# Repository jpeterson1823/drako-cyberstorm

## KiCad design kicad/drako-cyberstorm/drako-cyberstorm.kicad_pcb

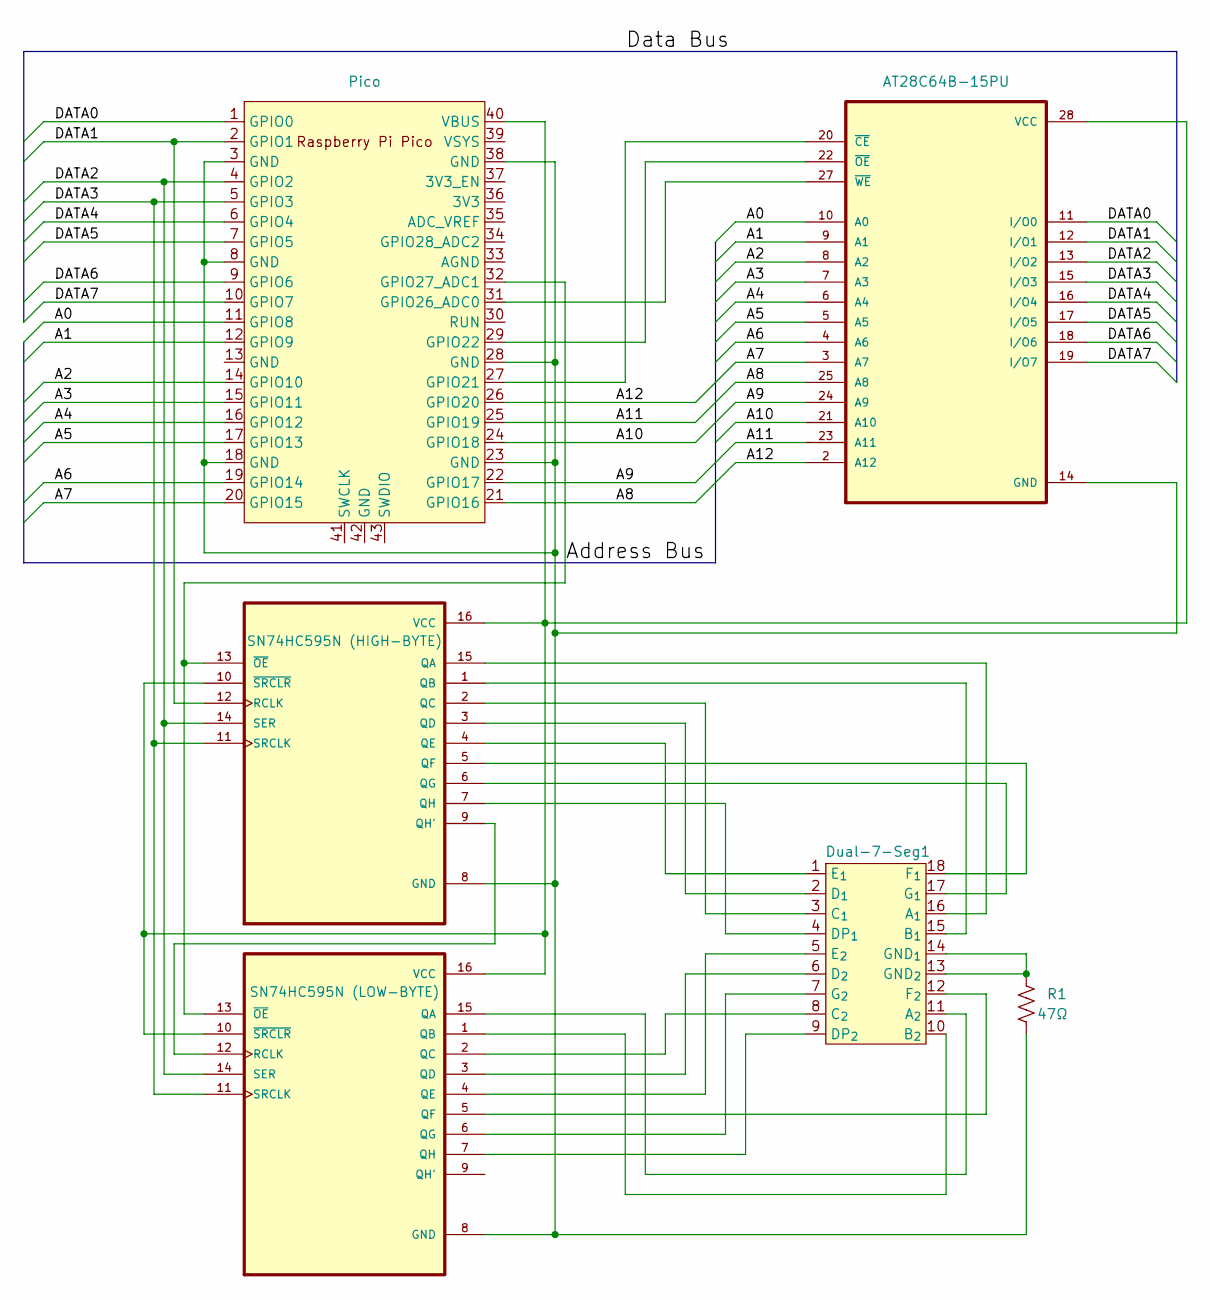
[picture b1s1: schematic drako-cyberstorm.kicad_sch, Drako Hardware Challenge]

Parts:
Dual-7-Seg1: LDD-C514RI
R1: 47Ω; R_Axial_DIN0207_L6.3mm_D2.5mm_P10.16mm_Horizontal
U1: Pico; RPi_Pico_SMD_TH
U2: AT28C64B-15PU; DIP1555W45P254L3733H482Q28; PARTREV B
U3: SN74HC595N (HIGH-BYTE); DIP794W45P254L1969H508Q16; DigiKey_Part_Number 296-1600-5-ND
U4: SN74HC595N (LOW-BYTE); DIP794W45P254L1969H508Q16; DigiKey_Part_Number 296-1600-5-ND

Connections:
/A0: U1.11 (GPIO8), U2.10 (A0)
/A1: U1.12 (GPIO9), U2.9 (A1)
/A2: U1.14 (GPIO10), U2.8 (A2)
/A3: U1.15 (GPIO11), U2.7 (A3)
/A4: U1.16 (GPIO12), U2.6 (A4)
/A5: U1.17 (GPIO13), U2.5 (A5)
/A6: U1.19 (GPIO14), U2.4 (A6)
/A7: U1.20 (GPIO15), U2.3 (A7)
/A8: U1.21 (GPIO16), U2.25 (A8)
/A9: U1.22 (GPIO17), U2.24 (A9)
/A10: U1.24 (GPIO18), U2.21 (A10)
/A11: U1.25 (GPIO19), U2.23 (A11)
/A12: U1.26 (GPIO20), U2.2 (A12)
/DATA0: U1.1 (GPIO0), U2.11 (I/O0)
/DATA1: U1.2 (GPIO1), U2.12 (I/O1), U3.12 (RCLK)
/DATA2: U1.4 (GPIO2), U2.13 (I/O2), U3.14 (SER), U4.14 (SER)
/DATA3: U1.5 (GPIO3), U2.15 (I/O3), U3.11 (SRCLK), U4.11 (SRCLK)
/DATA4: U1.6 (GPIO4), U2.16 (I/O4)
/DATA5: U1.7 (GPIO5), U2.17 (I/O5)
/DATA6: U1.9 (GPIO6), U2.18 (I/O6)
/DATA7: U1.10 (GPIO7), U2.19 (I/O7)
unnamed: Dual-7-Seg1.16 (A_{1}), U3.15 (QA)
unnamed: Dual-7-Seg1.11 (A_{2}), U4.15 (QA)
unnamed: Dual-7-Seg1.15 (B_{1}), U3.1 (QB)
unnamed: Dual-7-Seg1.10 (B_{2}), U4.1 (QB)
unnamed: Dual-7-Seg1.3 (C_{1}), U3.2 (QC)
unnamed: Dual-7-Seg1.8 (C_{2}), U4.2 (QC)
unnamed: Dual-7-Seg1.4 (DP_{1}), U3.7 (QH)
unnamed: Dual-7-Seg1.9 (DP_{2}), U4.7 (QH)
unnamed: Dual-7-Seg1.2 (D_{1}), U3.3 (QD)
unnamed: Dual-7-Seg1.6 (D_{2}), U4.3 (QD)
unnamed: Dual-7-Seg1.1 (E_{1}), U3.4 (QE)
unnamed: Dual-7-Seg1.5 (E_{2}), U4.4 (QE)
unnamed: Dual-7-Seg1.18 (F_{1}), U3.5 (QF)
unnamed: Dual-7-Seg1.12 (F_{2}), U4.5 (QF)
unnamed: Dual-7-Seg1.13 (GND_{2}), Dual-7-Seg1.14 (GND_{1}), R1.1
unnamed: Dual-7-Seg1.17 (G_{1}), U3.6 (QG)
unnamed: Dual-7-Seg1.7 (G_{2}), U4.6 (QG)
unnamed: U1.27 (GPIO21), U2.20 (~CE)
unnamed: U1.29 (GPIO22), U2.22 (~OE)
unnamed: U1.31 (GPIO26_ADC0), U2.27 (~WE)
unnamed: U1.32 (GPIO27_ADC1), U3.13 (~OE), U4.13 (~OE)
unnamed: U1.40 (VBUS), U2.28 (VCC), U3.10 (~SRCLR), U3.16 (VCC), U4.10 (~SRCLR), U4.16 (VCC)
unnamed: R1.2, U1.3 (GND), U1.8 (GND), U1.18 (GND), U1.23 (GND), U1.28 (GND), U1.38 (GND), U2.14 (GND), U3.8 (GND), U4.8 (GND)
unnamed: U3.9 (QH'), U4.12 (RCLK)

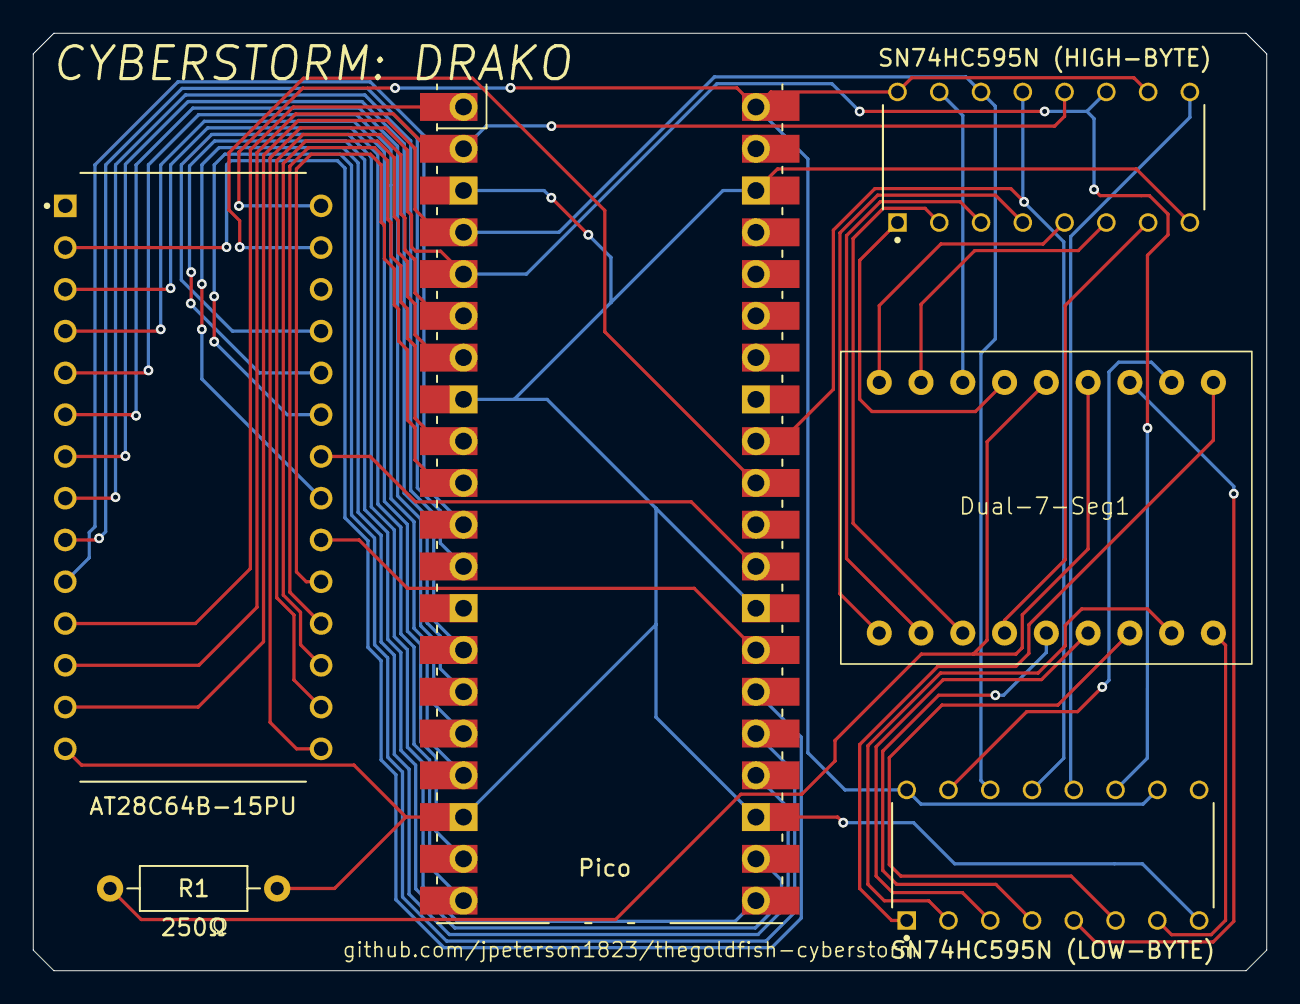
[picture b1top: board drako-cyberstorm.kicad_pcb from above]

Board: 2 copper layers, 75.0 x 57.0 mm, 6 parts (0 on the bottom side), 45 nets.

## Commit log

2024-12-25 Initializing this repo.
    Created:
    * SN74HC595 basic HAL
    * LDD-C514RI basic API (display)
    * Very basic hexidecimal Serial CLI
2025-01-01 HAL/API basic implementation completed.
    Basic control API for the display and HAL/API for the EEPROM is
    complete.
    Datasheet for EEPROM has been added.
2025-01-03 Completed PCB
    PCB for this challenge has been completed.
2025-01-03 Added the drawing sheet for KiCAD schematic and footprint
    Drawing sheet for this design was not included in the previous push. Adding it now.
2025-01-04 Started work on Drako's terminal and updated CMakeLists.
    CMakeLists was updated to use `pico-sdk` as a git submodule to aid in
    modularity of this repo.
2025-01-04 Renamed board to DRAKO & refactored code to match.
2025-01-04 Modified CMakeLists to use `pico-sdk` as submodule.
2025-01-22 Added early doxygen & continuing terminal progress.
2025-01-22 Implemented Randomized Full-Integration Test
2025-01-23 Fixed includes and made randomized test output more robust.
2025-01-23 Cleaned code up a bit and optimized terminal-api a little.
    TODO: terminal_get_command(...) still needs to split string and store
    arguments into the tcmd_t buffer.
2025-01-23 Terminal API completed. Started work on Drako's default commands.
2025-01-24 Refactored terminal-api code due to absolutely massively messing it up the first time.
2025-01-25 Terminal API optimizations and two new default commands.
    Removed all heap allocations and replaced them with stack allocations to
    avoid heap fragmentation. String manipulation was also made faster and
    safer by utilizing strtok_r and having robust null terminator
    guarantees.
    Two new commands: show and hide.
    Show displays a byte on the display.
2025-01-25 Removed merge artifact from CMakeLists.txt.
2025-01-26 Removed prebuilt Doxygen files and made some small aesthetic changes to some commands.
2025-01-31 Created new commands and sped up EEPROM code.
    Two new commands have been added:
    * steg
    * hexdump
    Reduced AT28C64B_CONDITION_DELAY_US from 100 to 5. No degredation to
    accuracy was found, however, going lower than this may cause EMI/RFI
    issues during CyberStorm due to the large volume of devices that will be
2025-02-04 Added xor_crypt(...) to drako library.
2025-02-10 Progress on Drako Flash API
    Flash Writing:
    * Can write data to flash in multiples of FLASH_BLOCKSIZE (4096 bytes)
    Flash Reading:
    * Variables exist, but methods not yet implemented.
    * Reading is possible, but only through use of #define's and such.
    TODO:
2025-02-10 Terminal API: added terminal_get_line_timed
2025-02-11 Completed Drako Datablock read methods.
    Write is not feasible for what we are doing, thus it has been removed
    and this branch renamed.
    I will be attempting to write a python script to allow for arbitrary
    data appendment to the UF2.
2025-02-18 Finished Level 0.
2025-02-18 Finished Level 1
2025-02-18 Fixed include guard for level0.
2025-02-18 Fixed include guard for level 1
2025-02-18 Actually finished level 1... fr.
2025-02-21 level 3 fails
2025-02-21 Mostly finish with Hidden Challenge
    TODO:
    * Implement All Challenge Flag Behavior
2025-02-21 Hidden Challenge Logic Complete.
    TODO:
    * Hints
2025-02-21 LEVEL 3 WORKS LETS GOOOOOOOOO
2025-02-21 Tweaked the steg to prevent file corruption of wrapper.
2025-02-21 Changed offset to be 250, which matches the incorrect resistor code.
2025-02-21 Updated level3: added final flag
2025-02-21 Updated Hidden Challenge Riddle.
2025-03-13 Added multiple hints, alternate solution paths, and updated challenge 2.
2025-03-18 Started Progress on rewrite of spaghetti code for challenge generator.
2025-03-18 Completed generation portion of the challenge generator rewrite.
    TODO: Print important information to console after generation is complete.
2025-03-26 Made good progress on challenge info display.
    TODO: Challenge 3 & 4 info display.
2025-03-26 Revived old generate.py script for demo purposes.
2025-03-26 Completed Challenge 3 & 4 Information Display
2025-03-27 Interfaced new generator with Drako API project structure.
2025-03-31 Refactored HC Generator Challenge code for better encapsulation.
2025-04-01 Completed Vigenere and XOR; Work needed on Caesar
    Caesar's decryption logic is flawed and needs rewrite.
2025-04-01 Generator's Caesar, Vigenere, and XOR methods fully implemented.
2025-04-03 Completed the generator and it's meshing with the Drako API.
    TODO:
    - Fix Drako Steg
    - Add XOR and VIGENERE commands to Drako API
    - Polish input/terminal controls
2025-04-15 HC Generator completed. DRAKO challenge is feature complete.
    TODO: Add range param to XOR and create Vigenere DRAKO command.
2025-04-21 Drako Hardware Challenge Completed.
2025-04-21 Finalized Schematic and PCB
    Moved shift registers' OE to GPIO 27 and edited the footprint silkscreen to better fit Louisiana Tech's CyberStorm event.
2025-04-25 Fixed Drako cmd parameter sanitization and display malfuction solved.
2025-04-30 Fixed display bug when HC_C2 credentials is unlocked.
